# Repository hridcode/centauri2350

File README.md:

# Centauri2350

Centauri2350 is a microcontroller board based off the RP2354B chip. It has 44 usable GPIO pins, plus battery charging and an audio DAC.

This is derived from my old board named "Whistle" (which honestly was trash lmao)

## Features

- 150MHz clock speed
- 520KB RAM
- 2MB flash memory
- 48 GPIOs (4 used for onboard LED + I²S connection)
- 8 analog-capable pins
- LiPo battery charging (IP5306)
- Audio DAC (PCM5102A)
- Debug pins
- USB-C connector

## Photos

### Schematic

### PCB

### 3D model

## BOM

|Part|Quantity|Price|Source|
|---|---|---|---|
|RP2354B|1|$1.620|[LCSC](https://www.lcsc.com/product-detail/C39843328.html)|
|PCM5102A|1|$1.360|[LCSC](https://www.lcsc.com/product-detail/C107671.html)|
|IP5306|1|$0.280|[LCSC](https://www.lcsc.com/product-detail/C181692.html)|
|XC6206P332MR|1|$0.130|[LCSC](https://www.lcsc.com/product-detail/C5446.html)|
|X322512MSB4SI|1|$0.100|[LCSC](https://www.lcsc.com/product-detail/C9002.html)|
|USB-C receptacle|1|$0.100|[LCSC](https://www.lcsc.com/product-detail/C165948.html)|
|3.9x2.9 switch|2|$0.150|[LCSC](https://www.lcsc.com/product-detail/C202388.html)|
|PCB|1|$1.600|[JLCPCB](https://cart.jlcpcb.com/quote?stencilLayer=2&stencilWidth=100&stencilLength=100&stencilCounts=5&plateType=1&spm=Jlcpcb.Homepage.1010)|
|0402 20pF capacitor|2|$0.027|[LCSC](https://www.lcsc.com/product-detail/C1554.html)|
|0402 0.1uF capacitor|16|$0.088|[LCSC](https://www.lcsc.com/product-detail/C1525.html)|
|0402 2.2uF capacitor|4|$0.026|[LCSC](https://www.lcsc.com/product-detail/C12530.html)|
|0402 4.7uF capacitor|3|$0.063|[LCSC](https://www.lcsc.com/product-detail/C23733.html)|
|0402 10uF capacitor|10|$0.284|[LCSC](https://www.lcsc.com/product-detail/C15525.html)|
|0603 22uF capacitor|3|$0.094|[LCSC](https://www.lcsc.com/product-detail/C59461.html)|
|0402 1uH inductor|1|$0.133|[LCSC](https://www.lcsc.com/product-detail/C84468.html)|
|0402 3.3uH inductor|1|$0.028|[LCSC](https://www.lcsc.com/product-detail/C84474.html)|
|0603 2Ω resistor|2|$0.008|[LCSC](https://www.lcsc.com/product-detail/C22977.html)|
|0603 27Ω resistor|2|$0.008|[LCSC](https://www.lcsc.com/product-detail/C25190.html)|
|0402 33Ω resistor|1|$0.007|[LCSC](https://www.lcsc.com/product-detail/C25105.html)|
|0402 470Ω resistor|2|$0.013|[LCSC](https://www.lcsc.com/product-detail/C25117.html)|
|0402 1KΩ resistor|2|$0.016|[LCSC](https://www.lcsc.com/product-detail/C11702.html)|
|0402 5.1KΩ resistor|2|$0.013|[LCSC](https://www.lcsc.com/product-detail/C25905.html)|
|0603 red LED|1|$0.007|[LCSC](https://www.lcsc.com/product-detail/C2286.html)|
|Total|1|$6.155||

## Notes

The firmware given is MicroPython firmware. Flash  onto the board by holding the boot button, plugging it into your computer, and dragging the .uf2 file onto the drive.

Pins marked with an asterisk (*) on the board are ADC pins.
Italicized pin names denote the debug pins.

Have fun making!

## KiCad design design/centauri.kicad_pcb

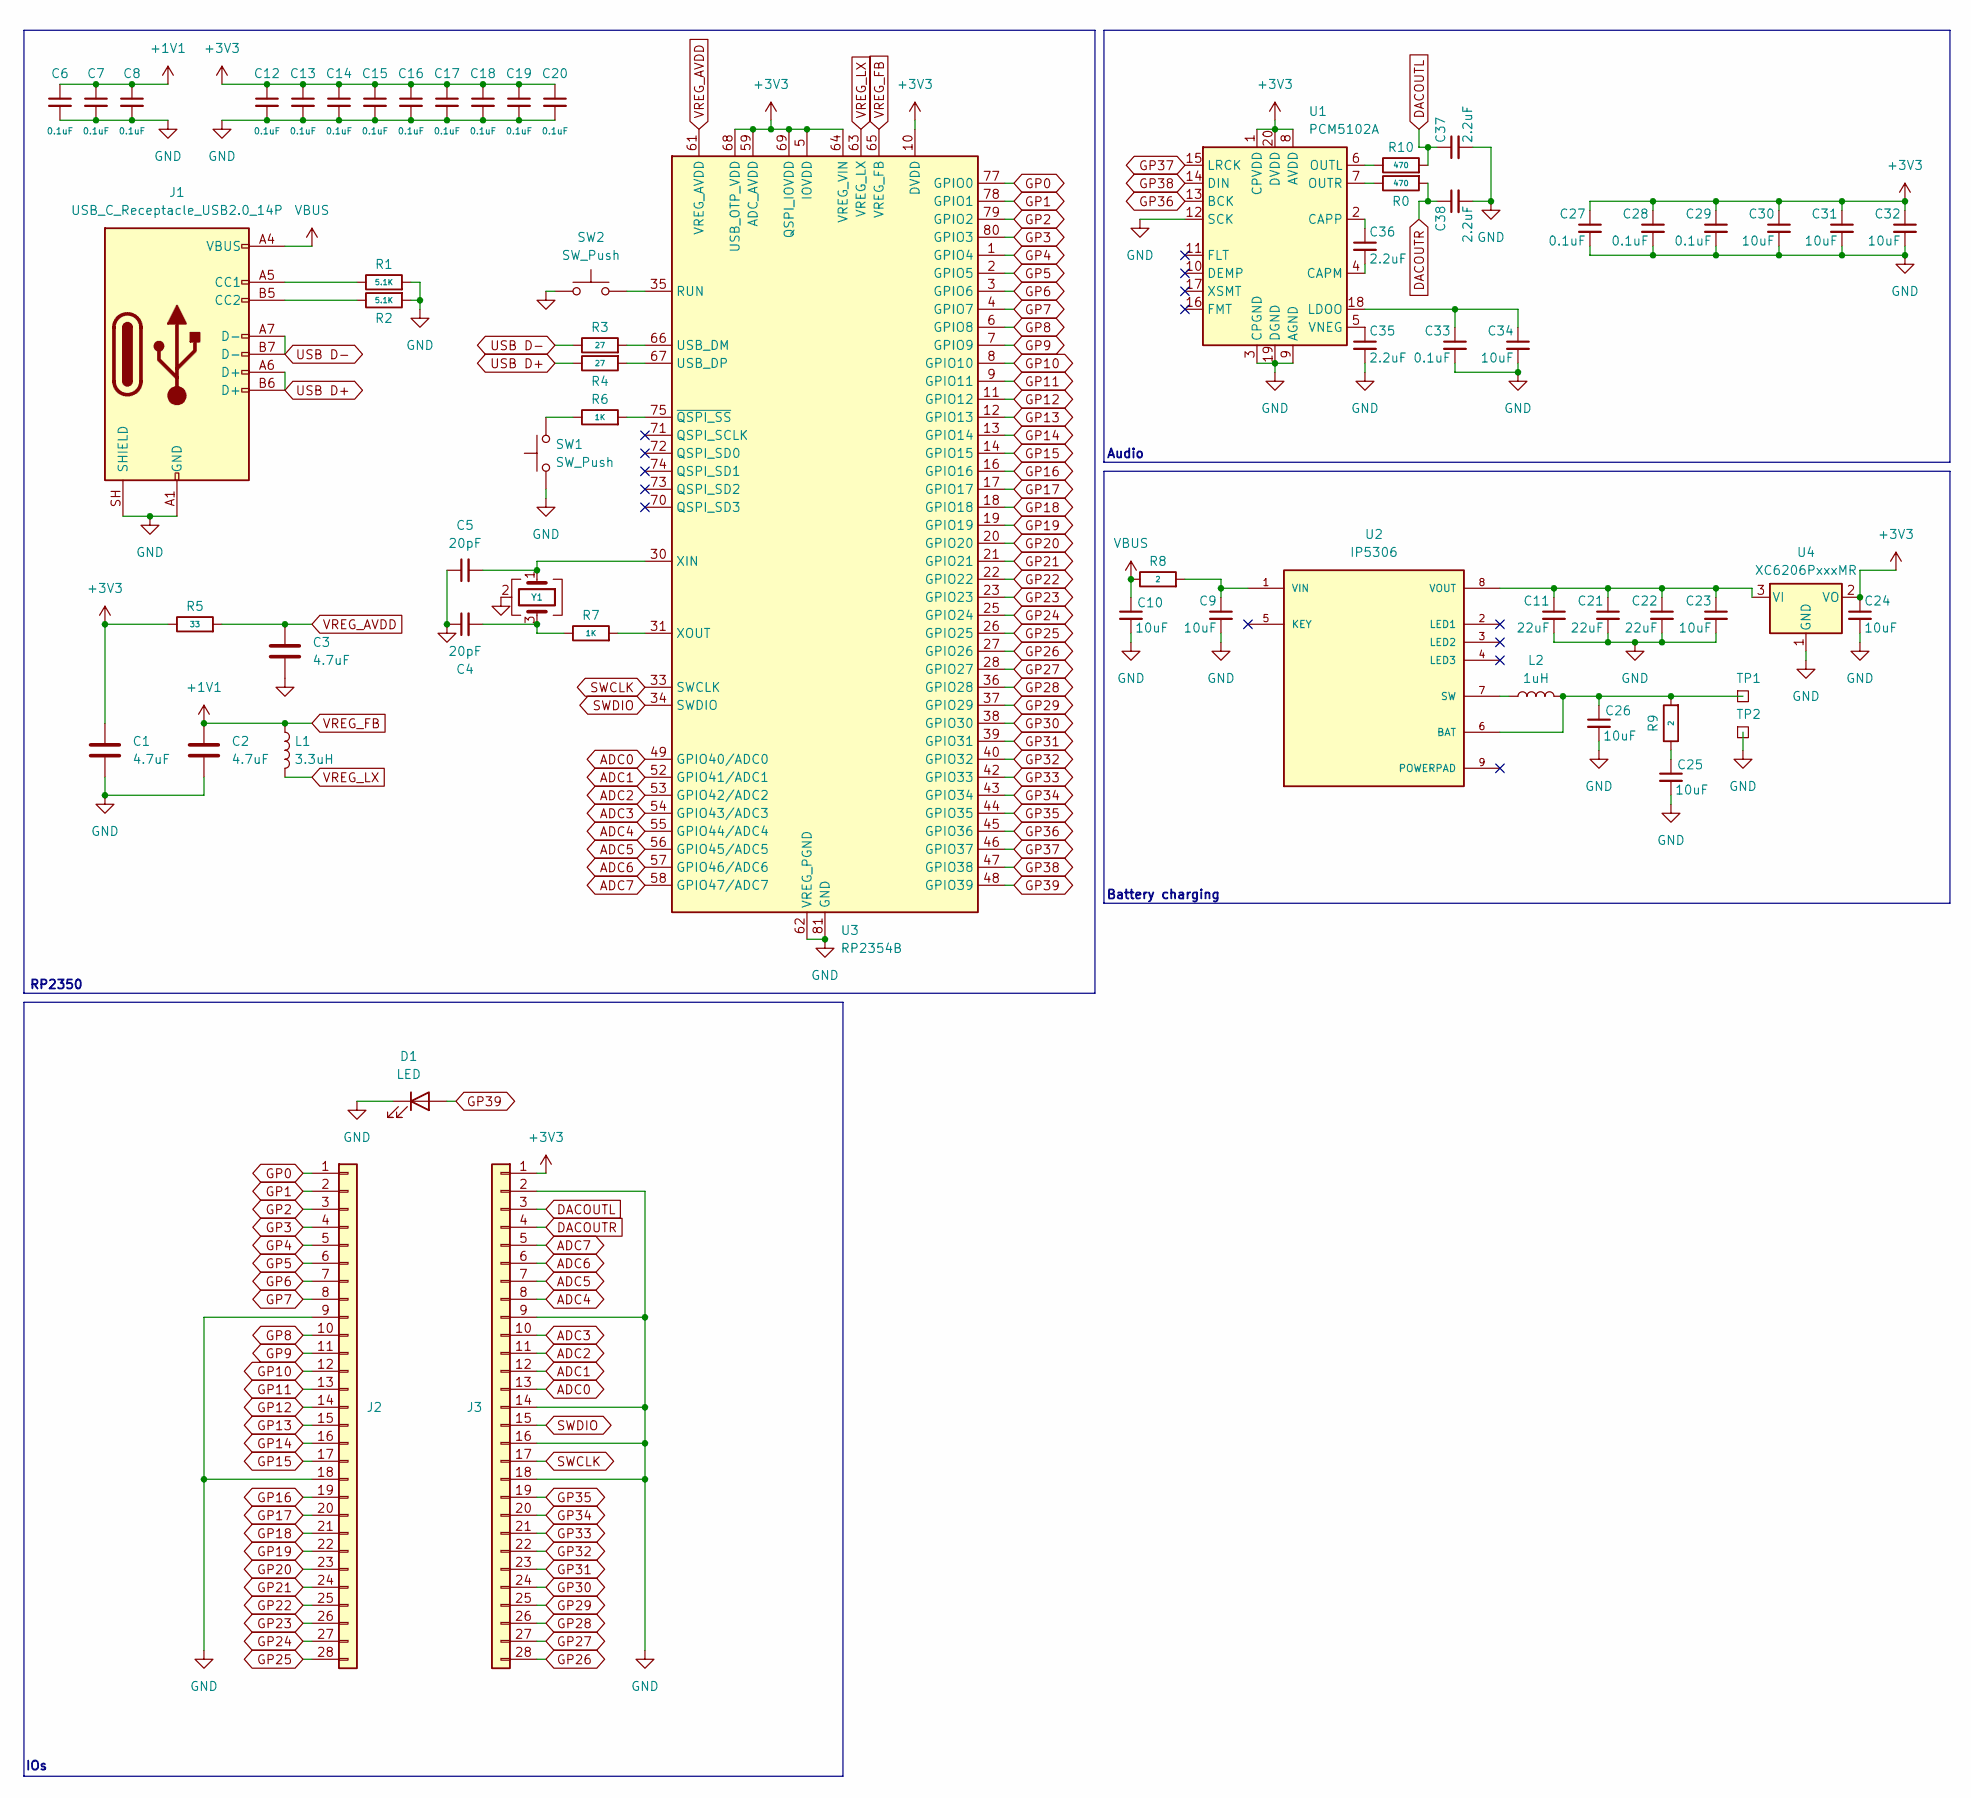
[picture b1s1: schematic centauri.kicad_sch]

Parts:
C1, C2, C3: 4.7uF; C_0402_1005Metric; MPN C23733
C4, C5: 20pF; C_0402_1005Metric; MPN C1554
C6, C7, C8, C12, C13, C14, C15, C16, C17, C18, C19, C20, C27, C28, C29, C33: 0.1uF; C_0402_1005Metric; MPN C1525
C9, C10, C23, C24, C25, C26, C30, C31, C32, C34: 10uF; C_0402_1005Metric; MPN C15525
C11, C21, C22: 22uF; C_0603_1608Metric; MPN C59461
C35, C36, C37, C38: 2.2uF; C_0402_1005Metric; MPN C12530
D1: LED; LED_0603_1608Metric; MPN C2286
J1: USB_C_Receptacle_USB2.0_14P; USB_C_Receptacle_HRO_TYPE-C-31-M-12; MPN C165948
J2, J3: Conn_01x28; PinHeader_1x28_P2.54mm_Vertical
L1: 3.3uH; L_0402_1005Metric; MPN C84474
L2: 1uH; L_0402_1005Metric; MPN C84468
R0, R10: 470; R_0402_1005Metric; MPN C25117
R1, R2: 5.1K; R_0402_1005Metric; MPN C25905
R3, R4: 27; R_0603_1608Metric; MPN C25190
R5: 33; R_0402_1005Metric; MPN C25105
R6, R7: 1K; R_0402_1005Metric; MPN C11702
R8, R9: 2; R_0603_1608Metric; MPN C22977
SW1, SW2: SW_Push; button_342
TP1, TP2: TestPoint_Square; TestPoint_Pad_2.5x2.5mm
U1: PCM5102A; TSSOP-20_4.4x6.5mm_P0.65mm; MPN C107671
U2: IP5306; eSOP-8; PARTREV 1.31
U3: RP2354B; QFN-80-1EP_10x10mm_P0.4mm_EP3.4x3.4mm; MPN C39843328
U4: XC6206PxxxMR; SOT-23-3; MPN C5446
Y1: Crystal_GND24; Crystal_SMD_3225-4Pin_3.2x2.5mm; MPN C9002

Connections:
+3V3: C1.1, C12.1, C13.1, C14.1, C15.1, C16.1, C17.1, C18.1, C19.1, C20.1, C24.1, C27.1, C28.1, C29.1, C30.1, C31.1, C32.1, J3.1, R5.1, U1.1 (CPVDD), U1.8 (AVDD), U1.20 (DVDD), U3.5 (IOVDD), U3.10 (DVDD), U3.15 (IOVDD), U3.24 (IOVDD), U3.29 (IOVDD), U3.32 (DVDD), U3.41 (IOVDD), U3.50 (IOVDD), U3.51 (DVDD), U3.59 (ADC_AVDD), U3.60 (IOVDD), U3.64 (VREG_VIN), U3.68 (USB_OTP_VDD), U3.69 (QSPI_IOVDD), U3.76 (IOVDD), U4.2 (VO)
ADC0: J3.13, U3.49 (GPIO40/ADC0)
ADC1: J3.12, U3.52 (GPIO41/ADC1)
ADC2: J3.11, U3.53 (GPIO42/ADC2)
ADC3: J3.10, U3.54 (GPIO43/ADC3)
ADC4: J3.8, U3.55 (GPIO44/ADC4)
ADC5: J3.7, U3.56 (GPIO45/ADC5)
ADC6: J3.6, U3.57 (GPIO46/ADC6)
ADC7: J3.5, U3.58 (GPIO47/ADC7)
DACOUTL: C37.1, J3.3, R10.2
DACOUTR: C38.1, J3.4, R0.2
GND: C1.2, C2.2, C3.2, C4.1, C5.1, C6.2, C7.2, C8.2, C9.2, C10.2, C11.2, C12.2, C13.2, C14.2, C15.2, C16.2, C17.2, C18.2, C19.2, C20.2, C21.2, C22.2, C23.2, C24.2, C25.2, C26.2, C27.2, C28.2, C29.2, C30.2, C31.2, C32.2, C33.2, C34.2, C35.2, C37.2, C38.2, D1.1 (K), J1.A1 (GND), J1.A12 (GND), J1.B1 (GND), J1.B12 (GND), J1.SH (SHIELD), J2.9, J2.18, J3.2, J3.9, J3.14, J3.16, J3.18, R1.2, R2.2, SW1.1, SW2.1, TP2.1 (1_1), U1.3 (CPGND), U1.9 (AGND), U1.12 (SCK), U1.19 (DGND), U3.62 (VREG_PGND), U3.81 (GND), U4.1 (GND), Y1.2 (G), Y1.4 (G)
GP0: J2.1, U3.77 (GPIO0)
GP1: J2.2, U3.78 (GPIO1)
GP2: J2.3, U3.79 (GPIO2)
GP3: J2.4, U3.80 (GPIO3)
GP4: J2.5, U3.1 (GPIO4)
GP5: J2.6, U3.2 (GPIO5)
GP6: J2.7, U3.3 (GPIO6)
GP7: J2.8, U3.4 (GPIO7)
GP8: J2.10, U3.6 (GPIO8)
GP9: J2.11, U3.7 (GPIO9)
GP10: J2.12, U3.8 (GPIO10)
GP11: J2.13, U3.9 (GPIO11)
GP12: J2.14, U3.11 (GPIO12)
GP13: J2.15, U3.12 (GPIO13)
GP14: J2.16, U3.13 (GPIO14)
GP15: J2.17, U3.14 (GPIO15)
GP16: J2.19, U3.16 (GPIO16)
GP17: J2.20, U3.17 (GPIO17)
GP18: J2.21, U3.18 (GPIO18)
GP19: J2.22, U3.19 (GPIO19)
GP20: J2.23, U3.20 (GPIO20)
GP21: J2.24, U3.21 (GPIO21)
GP22: J2.25, U3.22 (GPIO22)
GP23: J2.26, U3.23 (GPIO23)
GP24: J2.27, U3.25 (GPIO24)
GP25: J2.28, U3.26 (GPIO25)
GP26: J3.28, U3.27 (GPIO26)
GP27: J3.27, U3.28 (GPIO27)
GP28: J3.26, U3.36 (GPIO28)
GP29: J3.25, U3.37 (GPIO29)
GP30: J3.24, U3.38 (GPIO30)
GP31: J3.23, U3.39 (GPIO31)
GP32: J3.22, U3.40 (GPIO32)
GP33: J3.21, U3.42 (GPIO33)
GP34: J3.20, U3.43 (GPIO34)
GP35: J3.19, U3.44 (GPIO35)
GP36: U1.13 (BCK), U3.45 (GPIO36)
GP37: U1.15 (LRCK), U3.46 (GPIO37)
GP38: U1.14 (DIN), U3.47 (GPIO38)
GP39: D1.2 (A), U3.48 (GPIO39)
unnamed: C4.2, R7.1, Y1.3
unnamed: C25.1, R9.1
unnamed: J1.A5 (CC1), R1.1
unnamed: J1.B5 (CC2), R2.1
unnamed: R6.1, SW1.2
unnamed: C36.2, U1.4 (CAPM)
unnamed: C36.1, U1.2 (CAPP)
unnamed: C33.1, C34.1, U1.18 (LDOO)
unnamed: R10.1, U1.6 (OUTL)
unnamed: R0.1, U1.7 (OUTR)
unnamed: C35.1, U1.5 (VNEG)
unnamed: C26.1, L2.2, R9.2, TP1.1 (1_1), U2.6 (BAT)
unnamed: L2.1, U2.7 (SW)
unnamed: C9.1, R8.2, U2.1 (VIN)
unnamed: C11.1, C21.1, C22.1, C23.1, U2.8 (VOUT), U4.3 (VI)
unnamed: SW2.2, U3.35 (RUN)
unnamed: R3.2, U3.66 (USB_DM)
unnamed: R4.2, U3.67 (USB_DP)
unnamed: C5.2, U3.30 (XIN), Y1.1
unnamed: R7.2, U3.31 (XOUT)
unnamed: R6.2, U3.75 (~QSPI_SS)
SWCLK: J3.17, U3.33 (SWCLK)
SWDIO: J3.15, U3.34 (SWDIO)
USB D+: J1.A6 (D+), J1.B6 (D+), R4.1
USB D-: J1.A7 (D-), J1.B7 (D-), R3.1
VBUS: C10.1, J1.A4 (VBUS), J1.A9 (VBUS), J1.B4 (VBUS), J1.B9 (VBUS), R8.1
VREG_AVDD: C3.1, R5.2, U3.61 (VREG_AVDD)
VREG_FB: C2.1, C6.1, C7.1, C8.1, L1.1, U3.65 (VREG_FB)
VREG_LX: L1.2, U3.63 (VREG_LX)

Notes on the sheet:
Audio
Battery charging
RP2350
IOs

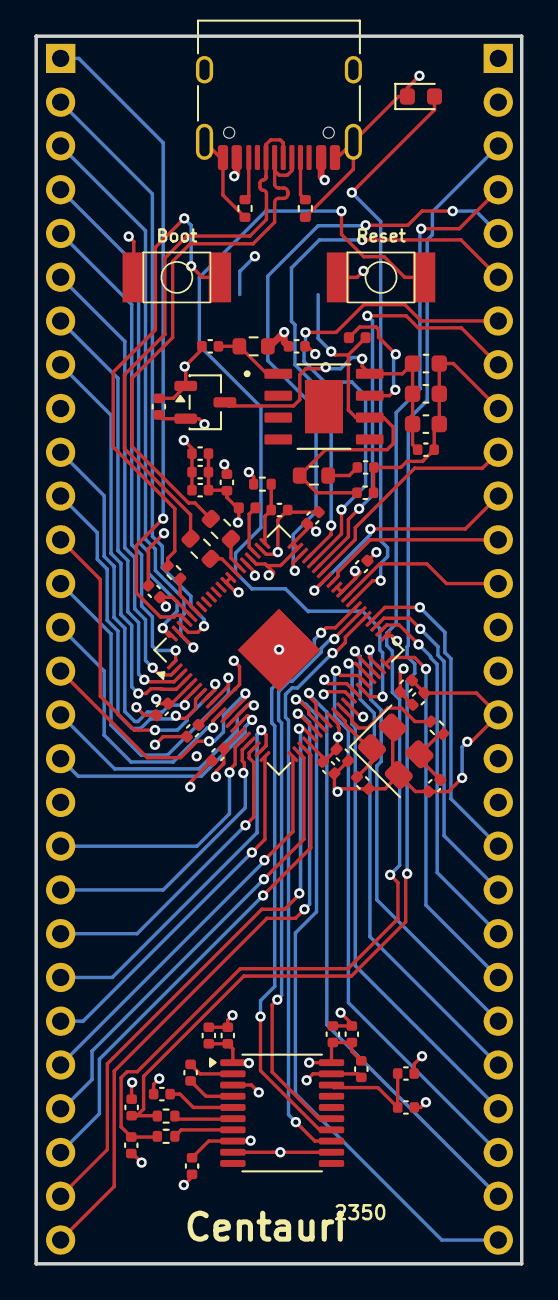
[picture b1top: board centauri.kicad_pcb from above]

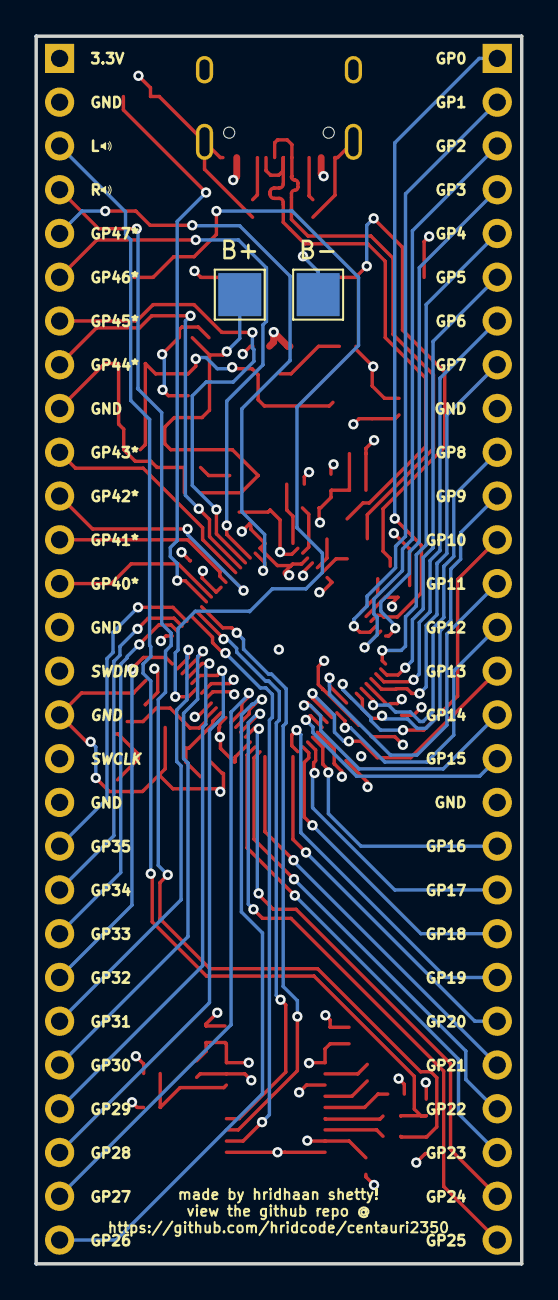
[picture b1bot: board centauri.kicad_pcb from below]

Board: 4 copper layers, 28.2 x 71.2 mm, 64 parts (4 on the bottom side), 81 nets.

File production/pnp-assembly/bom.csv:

Designator,Footprint,Quantity,Value,LCSC Part #
"C1, C2, C3",0402,3,4.7uF,C23733
"C10, C23, C24, C25, C26, C30, C31, C32, C34, C9",0402,10,10uF,C15525
"C11, C21, C22",0603,3,22uF,C59461
"C12, C13, C14, C15, C16, C17, C18, C19, C20, C27, C28, C29, C33, C6, C7, C8",0402,16,0.1uF,C1525
"C35, C36, C37, C38",0402,4,2.2uF,C12530
"C4, C5",0402,2,20pF,C1554
D1,0603,1,LED,C2286
J1,USB_C_Receptacle_HRO_TYPE-C-31-M-12,1,USB_C_Receptacle_USB2.0_14P,C165948
L1,0402,1,3.3uH,C84474
L2,0402,1,1uH,C84468
"R0, R10",0402,2,470,C25117
"R1, R2",0402,2,5.1K,C25905
"R3, R4",0603,2,27,C25190
R5,0402,1,33,C25105
"R6, R7",0402,2,1K,C11702
"R8, R9",0603,2,2,C22977
"SW1, SW2",button_342,2,SW_Push,
"TP1, TP2",TestPoint_Pad_2.5x2.5mm,2,TestPoint_Square,
U1,TSSOP-20_4.4x6.5mm_P0.65mm,1,PCM5102A,C107671
U2,eSOP-8,1,IP5306,C181692
U3,QFN-80-1EP_10x10mm_P0.4mm_EP3.4x3.4mm,1,RP2354B,C39843328
U4,SOT-23-3,1,XC6206PxxxMR,C5446
Y1,Crystal_SMD_3225-4Pin_3.2x2.5mm,1,Crystal_GND24,C9002
